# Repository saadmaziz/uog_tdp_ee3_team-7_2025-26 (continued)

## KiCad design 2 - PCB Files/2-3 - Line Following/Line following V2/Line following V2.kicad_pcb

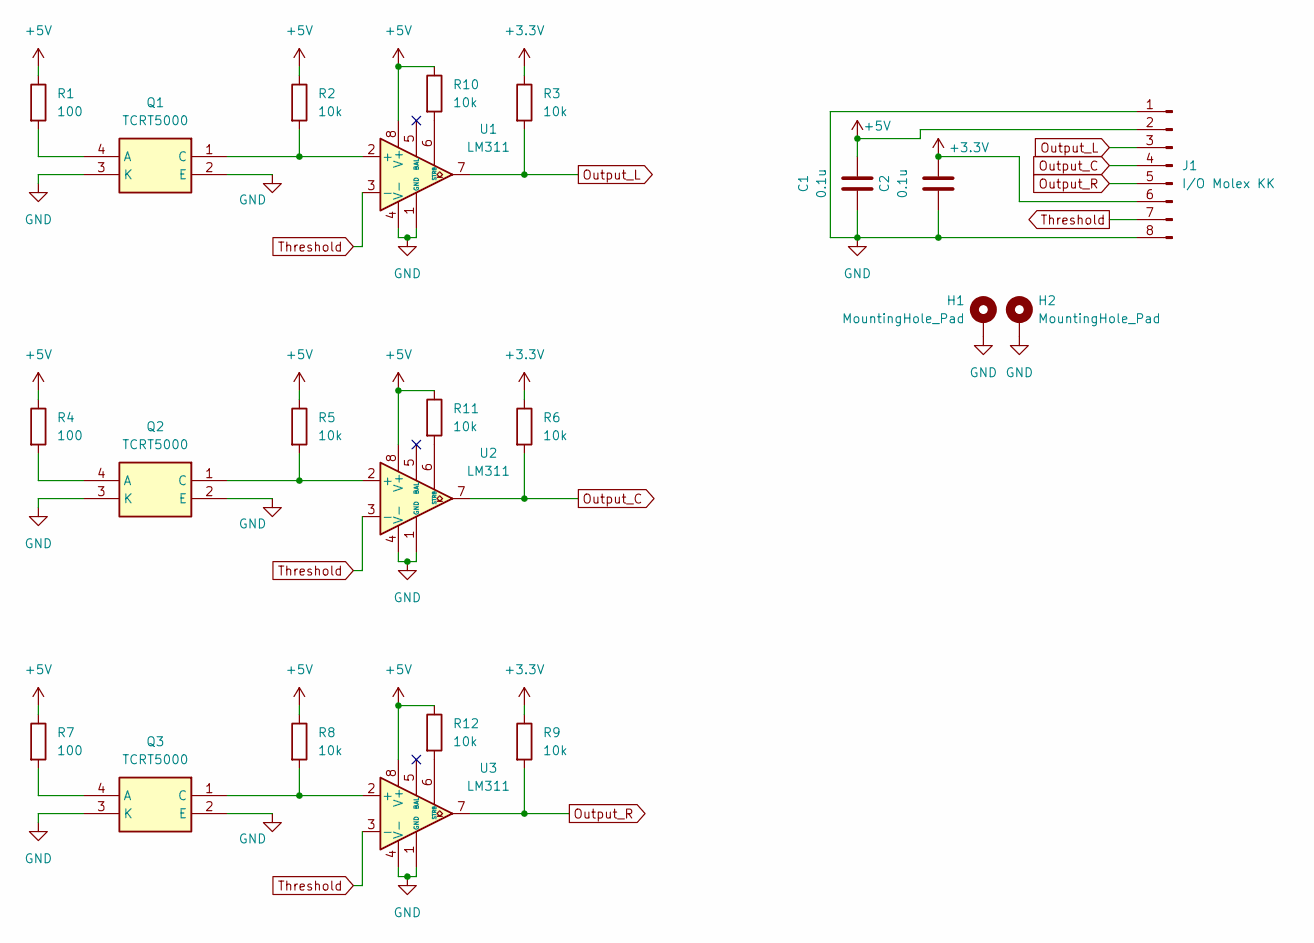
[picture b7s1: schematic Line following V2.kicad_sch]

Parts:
C1, C2: 0.1u; C_0805_2012Metric_Pad1.18x1.45mm_HandSolder
H1, H2: MountingHole_Pad; MountingHole_5.3mm_M5_DIN965_Pad_TopBottom
J1: I/O Molex KK; Molex_KK-254_AE-6410-08A_1x08_P2.54mm_Vertical
Q1, Q2, Q3: TCRT5000; Manufacturer_Part_Number TCRT5000
R1, R4, R7: 100; R_0805_2012Metric_Pad1.20x1.40mm_HandSolder
R2, R3, R5, R6, R8, R9, R10, R11, R12: 10k; R_0805_2012Metric_Pad1.20x1.40mm_HandSolder
U1, U2, U3: LM311; DIP-8_W7.62mm_LongPads

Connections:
+3.3V: C2.2, J1.6, R3.1, R6.1, R9.1
+5V: C1.2, J1.2, R1.1, R2.1, R4.1, R5.1, R7.1, R8.1, R10.1, R11.1, R12.1, U1.8 (V+), U2.8 (V+), U3.8 (V+)
GND: C1.1, C2.1, H1.1, H2.1, J1.1, J1.8, Q1.2 (E), Q1.3 (K), Q2.2 (E), Q2.3 (K), Q3.2 (E), Q3.3 (K), U1.1 (GND), U1.4 (V-), U2.1 (GND), U2.4 (V-), U3.1 (GND), U3.4 (V-)
unnamed: Q1.4 (A), R1.2
unnamed: Q1.1 (C), R2.2, U1.2 (+)
unnamed: Q2.4 (A), R4.2
unnamed: Q2.1 (C), R5.2, U2.2 (+)
unnamed: Q3.4 (A), R7.2
unnamed: Q3.1 (C), R8.2, U3.2 (+)
unnamed: R10.2, U1.6 (STRB)
unnamed: R11.2, U2.6 (STRB)
unnamed: R12.2, U3.6 (STRB)
Output_C: J1.4, R6.2, U2.7
Output_L: J1.3, R3.2, U1.7
Output_R: J1.5, R9.2, U3.7
Threshold: J1.7, U1.3 (-), U2.3 (-), U3.3 (-)

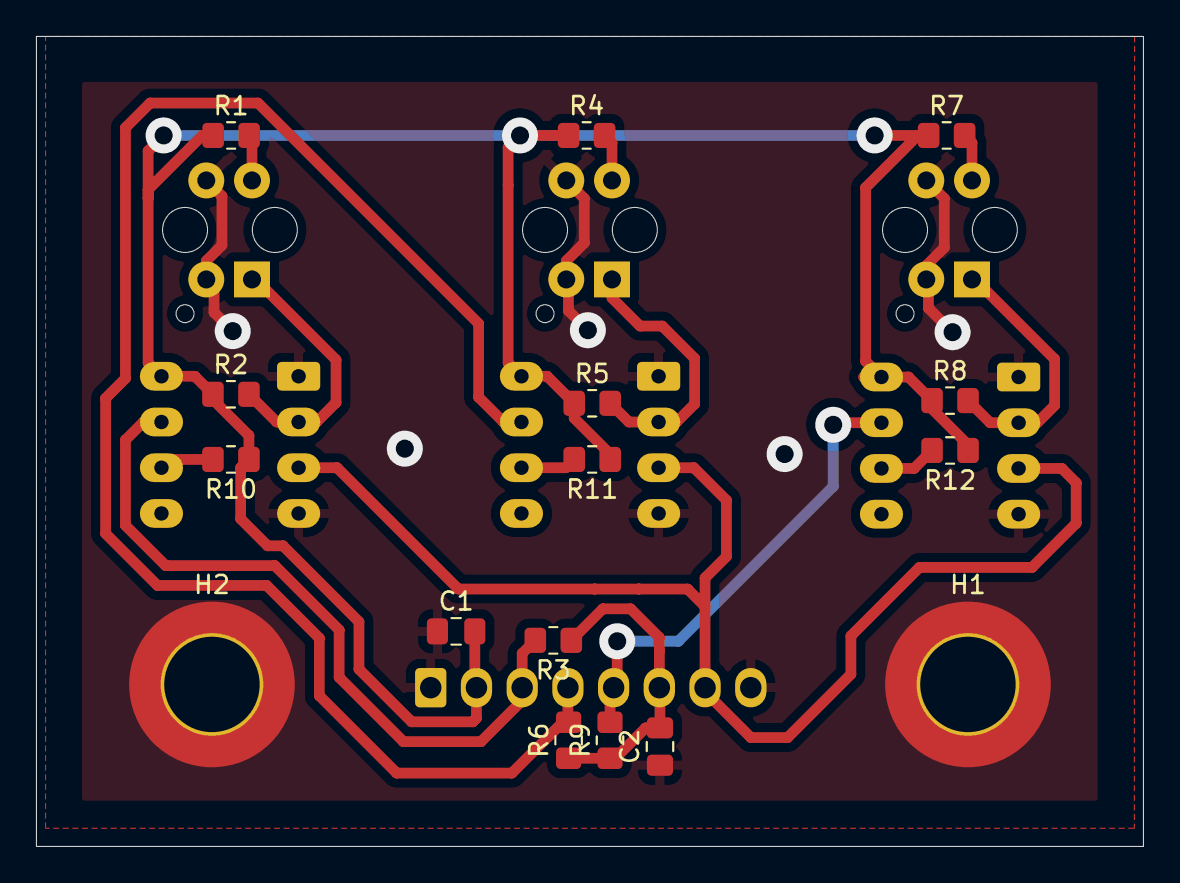
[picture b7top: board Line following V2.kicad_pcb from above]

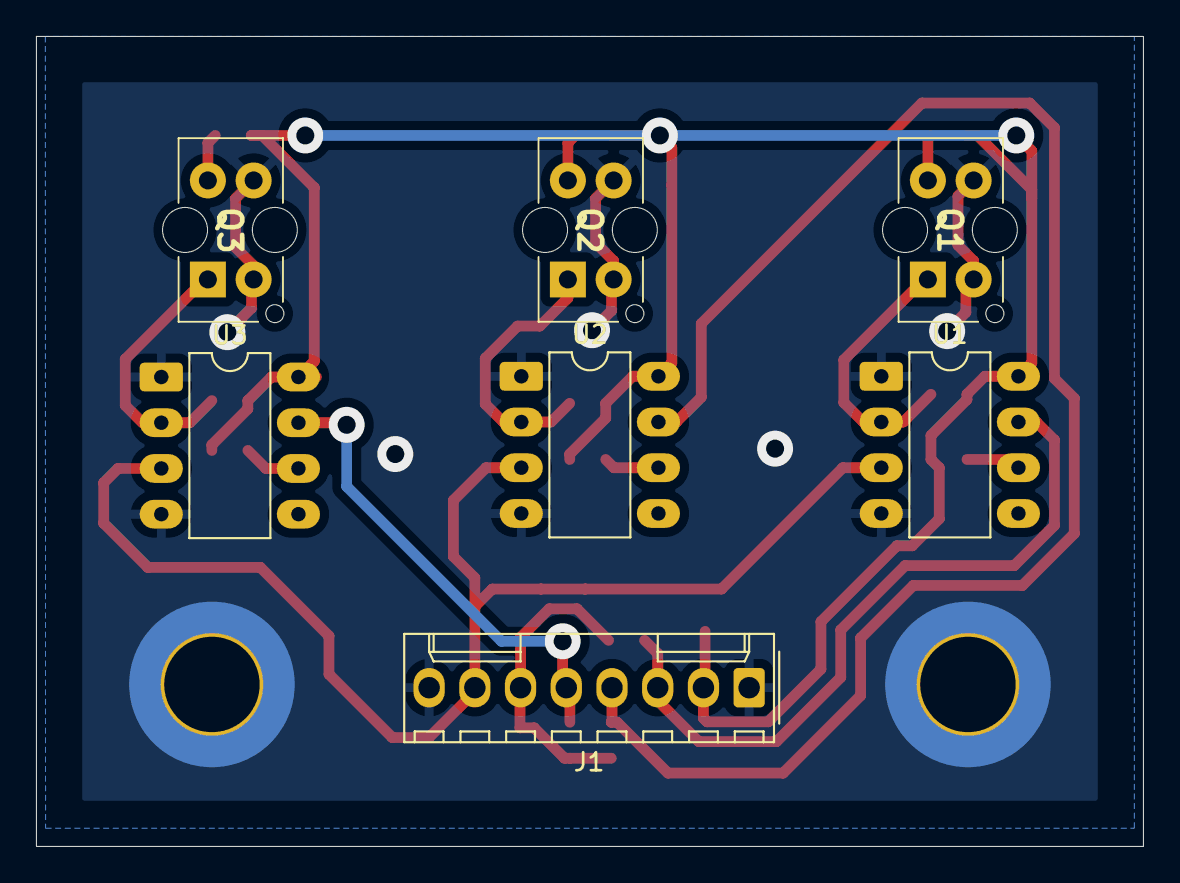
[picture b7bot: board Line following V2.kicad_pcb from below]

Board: 2 copper layers, 61.5 x 45.0 mm, 23 parts (7 on the bottom side), 16 nets.

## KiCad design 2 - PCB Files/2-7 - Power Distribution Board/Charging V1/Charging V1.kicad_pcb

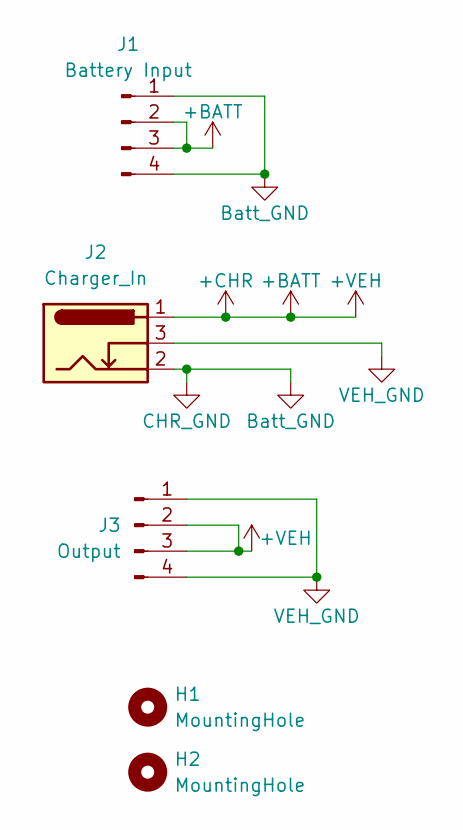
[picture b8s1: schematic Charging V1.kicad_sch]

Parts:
H1, H2: MountingHole; MountingHole_3.2mm_M3_DIN965
J1: Battery Input; Molex_KK-254_AE-6410-04A_1x04_P2.54mm_Vertical
J2: Charger_In; BarrelJack_GCT_DCJ200-10-A_Horizontal
J3: Output; Molex_KK-254_AE-6410-04A_1x04_P2.54mm_Vertical

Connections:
+BATT: J1.2, J1.3, J2.1, J3.2, J3.3
Batt_GND: J1.1, J1.4, J2.2
VEH_GND: J2.3, J3.1, J3.4

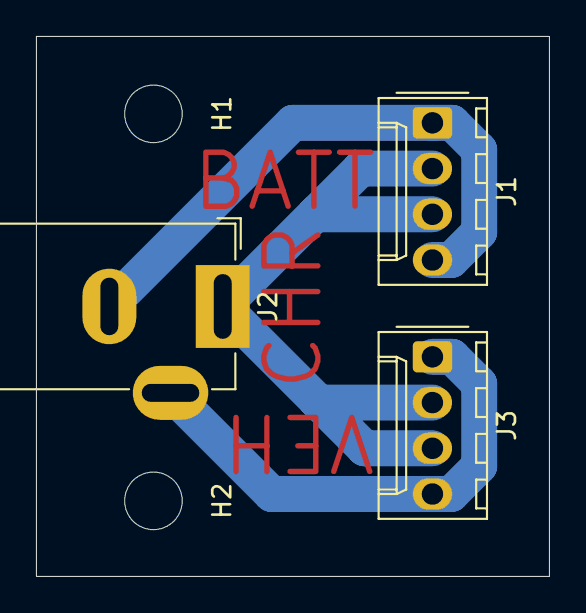
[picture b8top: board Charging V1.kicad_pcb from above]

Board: 2 copper layers, 28.5 x 30.0 mm, 5 parts (0 on the bottom side), 3 nets.

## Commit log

2026-03-15 Update project description in README.md
    Added details about remote control and central processor.
2026-04-17 Final Versions of all files
2026-04-17 Update README t
    Clarified the README by removing non-relevant information about team organization and documents.
2026-04-17 added final versions of code
2026-04-17 Added final code versions
2026-04-20 Update README with contributions.
    Specified personal contribution.
